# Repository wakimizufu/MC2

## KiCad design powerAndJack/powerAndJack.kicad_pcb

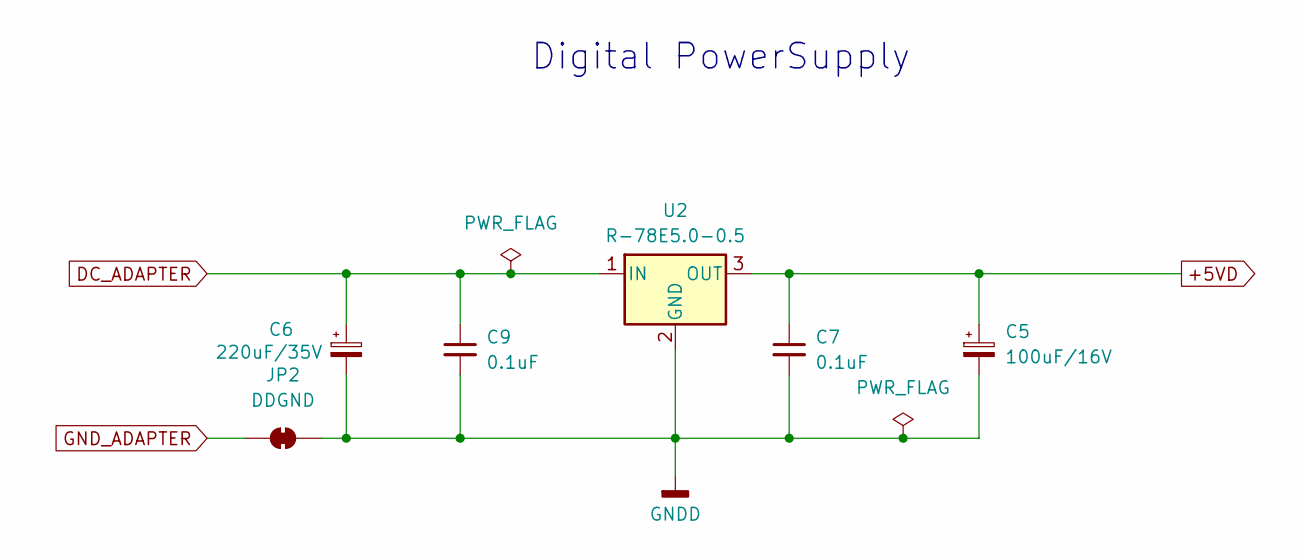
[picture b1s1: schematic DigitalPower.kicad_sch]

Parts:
C5: 100uF/16V; CP_Radial_D5.0mm_P2.00mm
C6: 220uF/35V; CP_Radial_D8.0mm_P3.50mm
C7, C9: 0.1uF; C_0805_2012Metric_Pad1.18x1.45mm_HandSolder
JP2: DDGND; SolderJumper-2_P1.3mm_Bridged2Bar_RoundedPad1.0x1.5mm
U2: R-78E5.0-0.5; Converter_DCDC_RECOM_R-78E-0.5_THT

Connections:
+5VD: C5.1, C7.1, U2.3 (OUT); also elsewhere on the board
DC_ADAPTER: C6.1, C9.1, U2.1 (IN); also elsewhere on the board
GNDD: C5.2, C6.2, C7.2, C9.2, JP2.2 (B), U2.2 (GND); also elsewhere on the board
GND_ADAPTER: JP2.1 (A); also elsewhere on the board

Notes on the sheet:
Digital PowerSupply

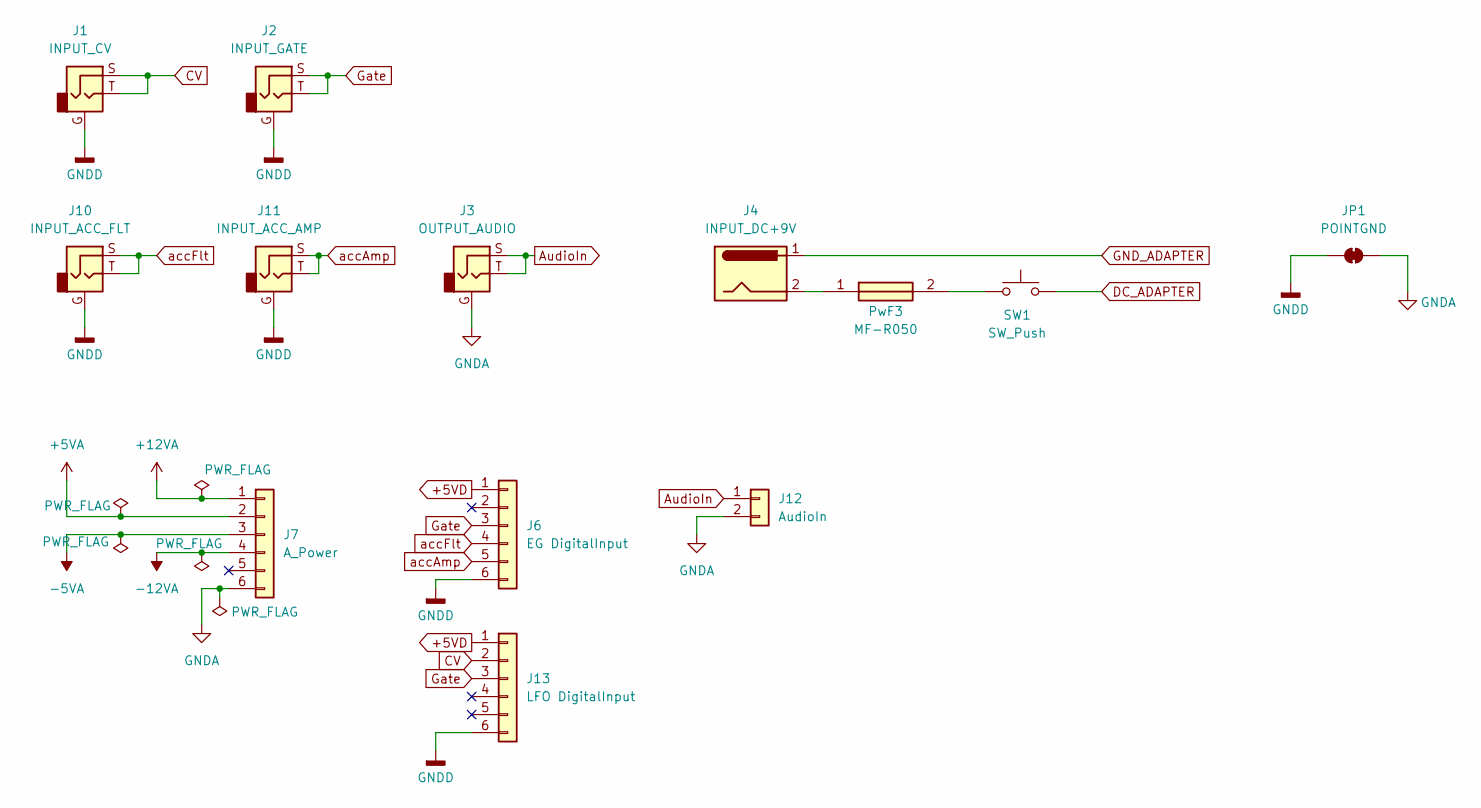
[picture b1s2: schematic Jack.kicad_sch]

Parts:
J1: INPUT_CV; MJ-355W
J2: INPUT_GATE; MJ-355W
J3: OUTPUT_AUDIO; MJ-355W
J4: INPUT_DC+9V; MJ-14
J6: EG DigitalInput; PinHeader_1x06_P2.54mm_Horizontal
J7: A_Power; PinHeader_1x06_P2.54mm_Horizontal
J10: INPUT_ACC_FLT; MJ-355W
J11: INPUT_ACC_AMP; MJ-355W
J12: AudioIn; PinHeader_1x02_P2.54mm_Horizontal
J13: LFO DigitalInput; PinHeader_1x06_P2.54mm_Horizontal
JP1: POINTGND; SolderJumper-2_P1.3mm_Bridged2Bar_RoundedPad1.0x1.5mm
PwF3: MF-R050; MFR050; Manufacturer_Part_Number MF-R050; Mouser Part Number 652-MFR050
SW1: SW_Push; mitumi DS660RC

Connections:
+5VA: J7.2; also elsewhere on the board
+5VD: J6.1, J13.1; also elsewhere on the board
+12VA: J7.1; also elsewhere on the board
-5VA: J7.3; also elsewhere on the board
-12VA: J7.4; also elsewhere on the board
AudioIn: J3.S, J3.T, J12.1
CV: J1.S, J1.T, J13.2
DC_ADAPTER: SW1.2; also elsewhere on the board
GNDA: J3.G, J7.6, J12.2, JP1.2 (B); also elsewhere on the board
GNDD: J1.G, J2.G, J6.6, J10.G, J11.G, J13.6, JP1.1 (A); also elsewhere on the board
GND_ADAPTER: J4.1; also elsewhere on the board
Gate: J2.S, J2.T, J6.3, J13.3
unnamed: J4.2, PwF3.1
unnamed: PwF3.2, SW1.1
accAmp: J6.5, J11.S, J11.T
accFlt: J6.4, J10.S, J10.T

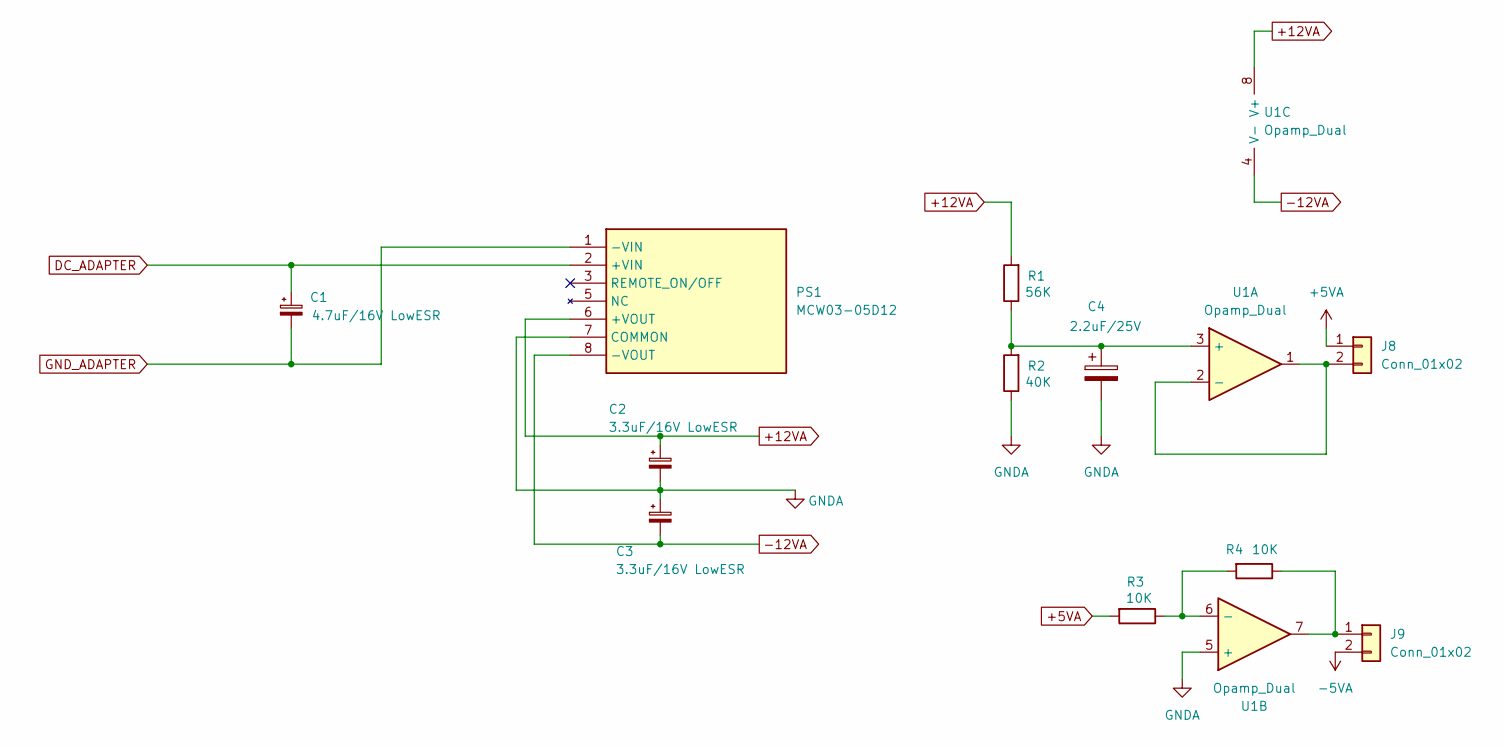
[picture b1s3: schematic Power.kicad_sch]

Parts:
C1: 4.7uF/16V LowESR; CP_Radial_D5.0mm_P2.50mm
C2, C3: 3.3uF/16V LowESR; CP_Radial_D5.0mm_P2.50mm
C4: 2.2uF/25V; CP_Radial_D5.0mm_P2.50mm
J8, J9: Conn_01x02; PinHeader_1x02_P2.54mm_Vertical
PS1: MCW03-05D12; MCW0305D12; Manufacturer_Part_Number MCW03-05D12
R1: 56K; R_Axial_DIN0207_L6.3mm_D2.5mm_P2.54mm_Vertical
R2: 40K; R_Axial_DIN0207_L6.3mm_D2.5mm_P2.54mm_Vertical
R3, R4: 10K; R_Axial_DIN0207_L6.3mm_D2.5mm_P2.54mm_Vertical
U1: Opamp_Dual; SOIC-8_3.9x4.9mm_P1.27mm

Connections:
+5VA: J8.1, R3.2; also elsewhere on the board
+12VA: C2.1, PS1.6 (+VOUT), R1.2, U1.8 (V+); also elsewhere on the board
-5VA: J9.2; also elsewhere on the board
-12VA: C3.2, PS1.8 (-VOUT), U1.4 (V-); also elsewhere on the board
DC_ADAPTER: C1.1, PS1.2 (+VIN); also elsewhere on the board
GNDA: C2.2, C3.1, C4.2, PS1.7 (COMMON), R2.1, U1.5 (+); also elsewhere on the board
GND_ADAPTER: C1.2, PS1.1 (-VIN); also elsewhere on the board
unnamed: J8.2, U1.1, U1.2 (-)
unnamed: J9.1, R4.1, U1.7
unnamed: C4.1, R1.1, R2.2, U1.3 (+)
unnamed: R3.1, R4.2, U1.6 (-)

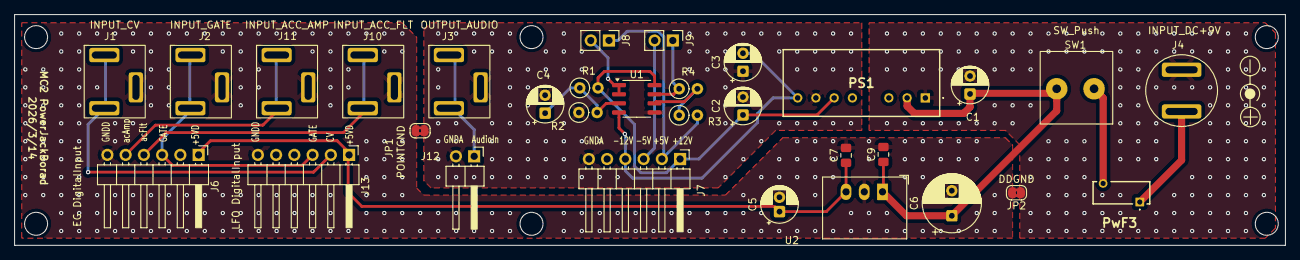
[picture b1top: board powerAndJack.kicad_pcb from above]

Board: 2 copper layers, 177.0 x 32.1 mm, 31 parts (0 on the bottom side), 20 nets.

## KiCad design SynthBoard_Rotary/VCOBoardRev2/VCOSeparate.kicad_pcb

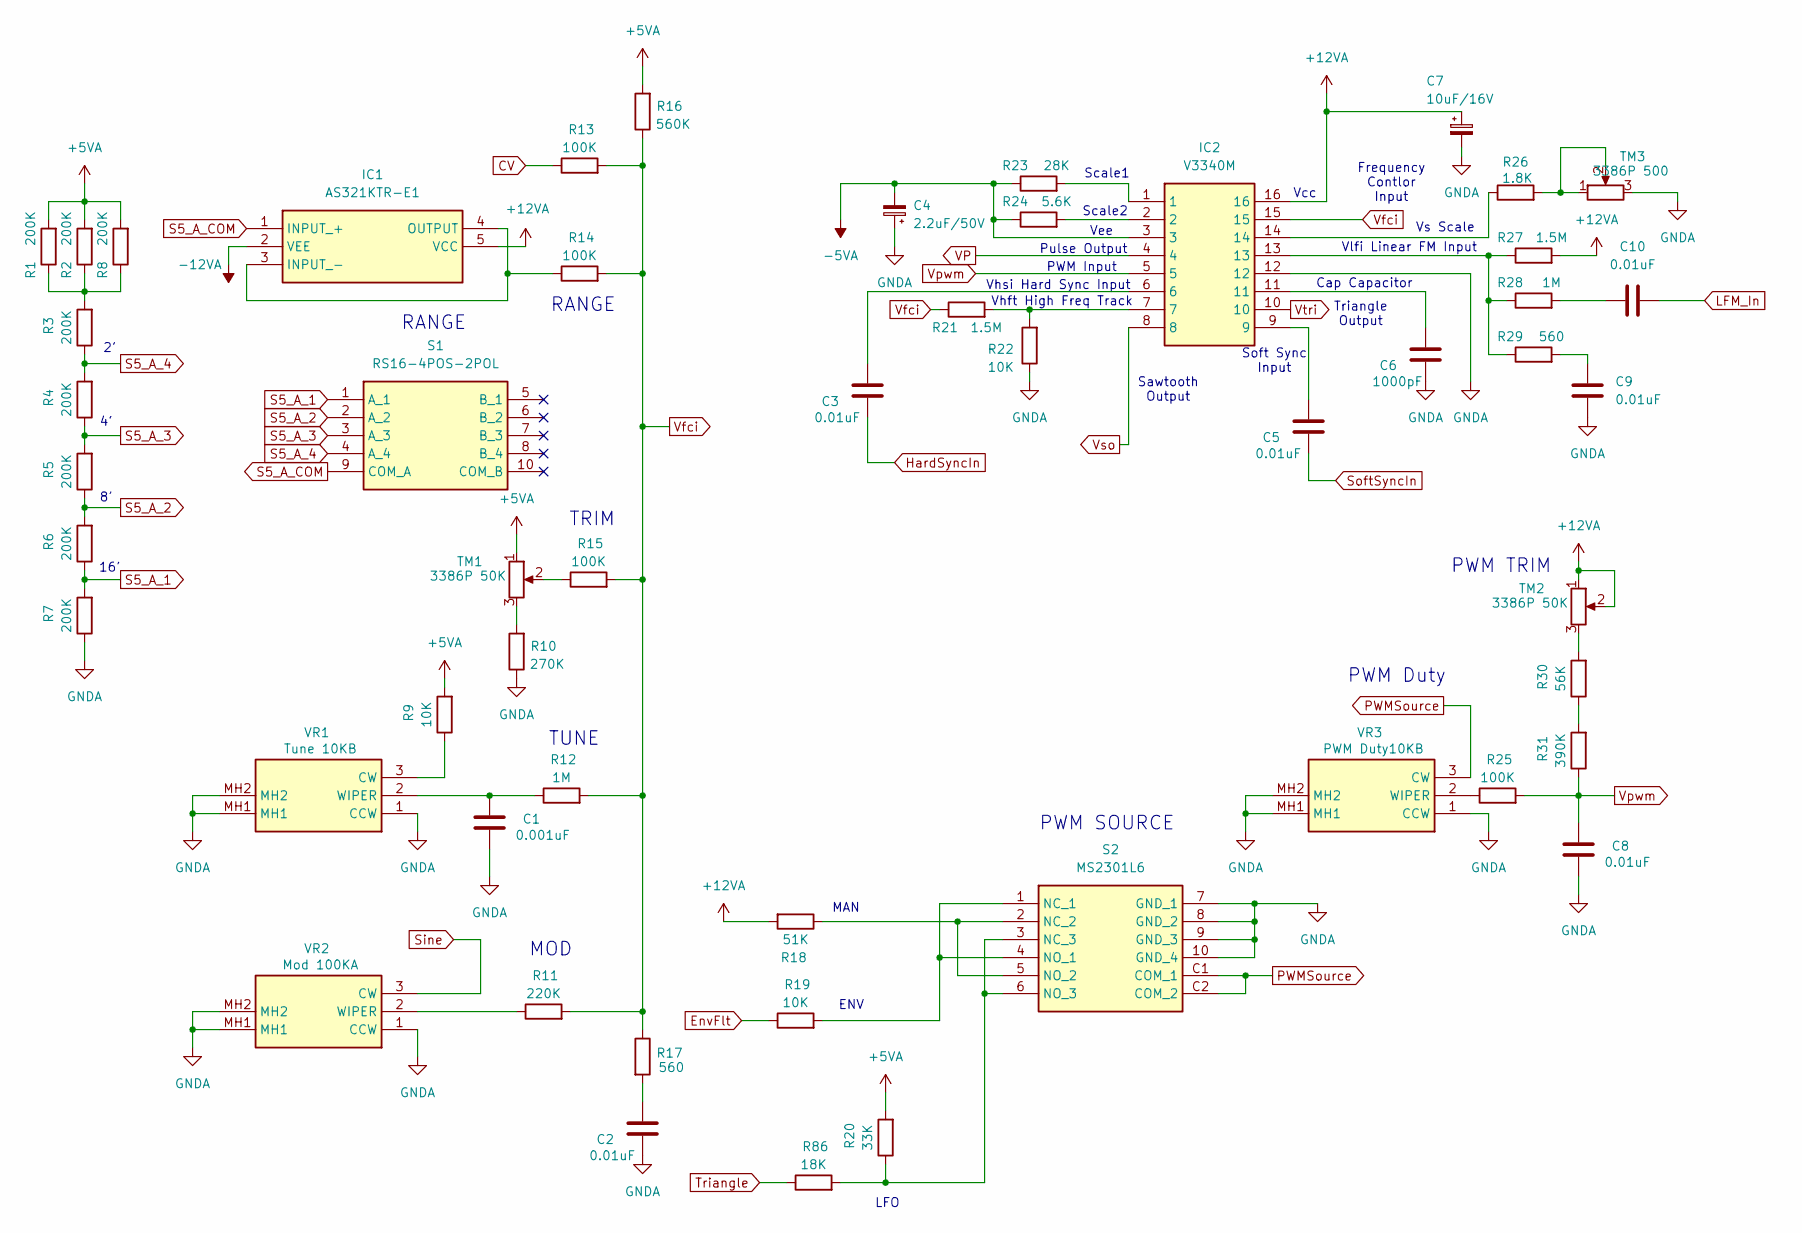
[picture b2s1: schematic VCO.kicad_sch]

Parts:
C1: 0.001uF; C_Disc_D5.0mm_W2.5mm_P2.50mm
C2, C3, C5, C8, C9, C10: 0.01uF; C_Disc_D5.0mm_W2.5mm_P2.50mm
C4: 2.2uF/50V; CP_Radial_D5.0mm_P2.50mm
C6: 1000pF; C_Disc_D5.0mm_W2.5mm_P2.50mm
C7: 10uF/16V; CP_Radial_D5.0mm_P2.50mm
IC1: AS321KTR-E1; SOT95P282X145-5N; Manufacturer_Part_Number AS321KTR-E1; Mouser Part Number 621-AS321KTR-E1
IC2: V3340M; SOP-16_3.9x9.9mm_P1.27mm; Manufacturer_Part_Number V3340M
R1, R2, R3, R4, R5, R6, R7, R8: 200K; R_Axial_DIN0207_L6.3mm_D2.5mm_P2.54mm_Vertical
R9, R19, R22: 10K; R_Axial_DIN0207_L6.3mm_D2.5mm_P2.54mm_Vertical
R10: 270K; R_Axial_DIN0207_L6.3mm_D2.5mm_P2.54mm_Vertical
R11: 220K; R_Axial_DIN0207_L6.3mm_D2.5mm_P2.54mm_Vertical
R12, R28: 1M; R_Axial_DIN0207_L6.3mm_D2.5mm_P2.54mm_Vertical
R13, R14, R15, R25: 100K; R_Axial_DIN0207_L6.3mm_D2.5mm_P2.54mm_Vertical
R16: 560K; R_Axial_DIN0207_L6.3mm_D2.5mm_P2.54mm_Vertical
R17, R29: 560; R_Axial_DIN0207_L6.3mm_D2.5mm_P2.54mm_Vertical
R18: 51K; R_Axial_DIN0207_L6.3mm_D2.5mm_P2.54mm_Vertical
R20: 33K; R_Axial_DIN0207_L6.3mm_D2.5mm_P2.54mm_Vertical
R21, R27: 1.5M; R_Axial_DIN0207_L6.3mm_D2.5mm_P2.54mm_Vertical
R23: 28K; R_Axial_DIN0207_L6.3mm_D2.5mm_P2.54mm_Vertical
R24: 5.6K; R_Axial_DIN0207_L6.3mm_D2.5mm_P2.54mm_Vertical
R26: 1.8K; R_Axial_DIN0207_L6.3mm_D2.5mm_P2.54mm_Vertical
R30: 56K; R_Axial_DIN0207_L6.3mm_D2.5mm_P2.54mm_Vertical
R31: 390K; R_Axial_DIN0207_L6.3mm_D2.5mm_P2.54mm_Vertical
R86: 18K; R_Axial_DIN0207_L6.3mm_D2.5mm_P2.54mm_Vertical
S1: RS16-4POS-2POL; RS164POS2POL; Manufacturer_Part_Number RS16-4POS-2POL
S2: MS2301L6; Manufacturer_Part_Number MS2301L6
TM1, TM2: 3386P 50K; Potentiometer_Bourns_3386P_Vertical
TM3: 3386P 500; Potentiometer_Bourns_3386P_Vertical
VR1: Tune 10KB; RK09D117000B; Manufacturer_Part_Number RK09D117000B; Mouser Part Number 688-RK09D117000B
VR2: Mod 100KA; RK09D117000B; Manufacturer_Part_Number RK09D117000B; Mouser Part Number 688-RK09D117000B
VR3: PWM Duty10KB; RK09D117000B; Manufacturer_Part_Number RK09D117000B; Mouser Part Number 688-RK09D117000B

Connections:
+5VA: R1.2, R2.2, R8.2, R9.2, R16.2, R20.2, TM1.1; also elsewhere on the board
+12VA: C7.1, IC1.5 (VCC), IC2.16, R18.2, R27.2, TM2.1, TM2.2; also elsewhere on the board
-5VA: C4.2, IC2.3, R23.1, R24.1; also elsewhere on the board
-12VA: IC1.2 (VEE); also elsewhere on the board
CV: R13.1; also elsewhere on the board
EnvFlt: R19.1; also elsewhere on the board
GNDA: C1.1, C2.1, C4.1, C6.1, C7.2, C8.1, C9.1, IC2.12, R7.1, R10.1, R22.1, S2.7 (GND_1), S2.8 (GND_2), S2.9 (GND_3), S2.10 (GND_4), TM3.3, VR1.1 (CCW), VR1.MH1, VR1.MH2, VR2.1 (CCW), VR2.MH1, VR2.MH2, VR3.1 (CCW), VR3.MH1, VR3.MH2; also elsewhere on the board
HardSyncIn: C3.1; also elsewhere on the board
LFM_In: C10.1; also elsewhere on the board
unnamed: C2.2, R17.2
unnamed: C3.2, IC2.6
unnamed: C5.2, IC2.9
unnamed: C6.2, IC2.11
unnamed: C9.2, R29.2
unnamed: C10.2, R28.2
unnamed: IC1.3 (INPUT_-), IC1.4 (OUTPUT), R14.1
unnamed: IC2.1, R23.2
unnamed: IC2.2, R24.2
unnamed: IC2.7, R21.2, R22.2
unnamed: IC2.13, R27.1, R28.1, R29.1
unnamed: IC2.14, R26.1
unnamed: R1.1, R2.1, R3.2, R8.1
unnamed: R10.2, TM1.3
unnamed: R15.1, TM1.2
unnamed: R26.2, TM3.1, TM3.2
unnamed: R30.1, R31.2
unnamed: R30.2, TM2.3
unnamed: R19.2, S2.1 (NC_1), S2.4 (NO_1)
unnamed: R18.1, S2.2 (NC_2), S2.5 (NO_2)
unnamed: R20.1, R86.2, S2.3 (NC_3), S2.6 (NO_3)
unnamed: R9.1, VR1.3 (CW)
unnamed: C1.2, R12.1, VR1.2 (WIPER)
unnamed: R11.1, VR2.2 (WIPER)
unnamed: R25.1, VR3.2 (WIPER)
PWMSource: S2.C1 (COM_1), S2.C2 (COM_2), VR3.3 (CW)
S5_A_1: R6.1, R7.2, S1.1 (A_1)
S5_A_2: R5.1, R6.2, S1.2 (A_2)
S5_A_3: R4.1, R5.2, S1.3 (A_3)
S5_A_4: R3.1, R4.2, S1.4 (A_4)
S5_A_COM: IC1.1 (INPUT_+), S1.9 (COM_A)
Sine: VR2.3 (CW); also elsewhere on the board
SoftSyncIn: C5.1; also elsewhere on the board
Triangle: R86.1; also elsewhere on the board
VP: IC2.4; also elsewhere on the board
Vfci: IC2.15, R11.2, R12.2, R13.2, R14.2, R15.2, R16.1, R17.1, R21.1
Vpwm: C8.2, IC2.5, R25.2, R31.1
Vso: IC2.8; also elsewhere on the board
Vtri: IC2.10; also elsewhere on the board

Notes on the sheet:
Vhft High Freq Track
LFO
TRIM
MOD
Vee
MAN
Sawtooth Output
PWM Input
RANGE
Vcc
PWM SOURCE
Vhsi Hard Sync Input
PWM TRIM
Vlfi Linear FM Input
16'
Pulse Output
Vs Scale
Scale1
Scale2
Triangle Output
Cap Capacitor
PWM Duty
Frequency Contlor Input
Soft Sync Input
TUNE
ENV

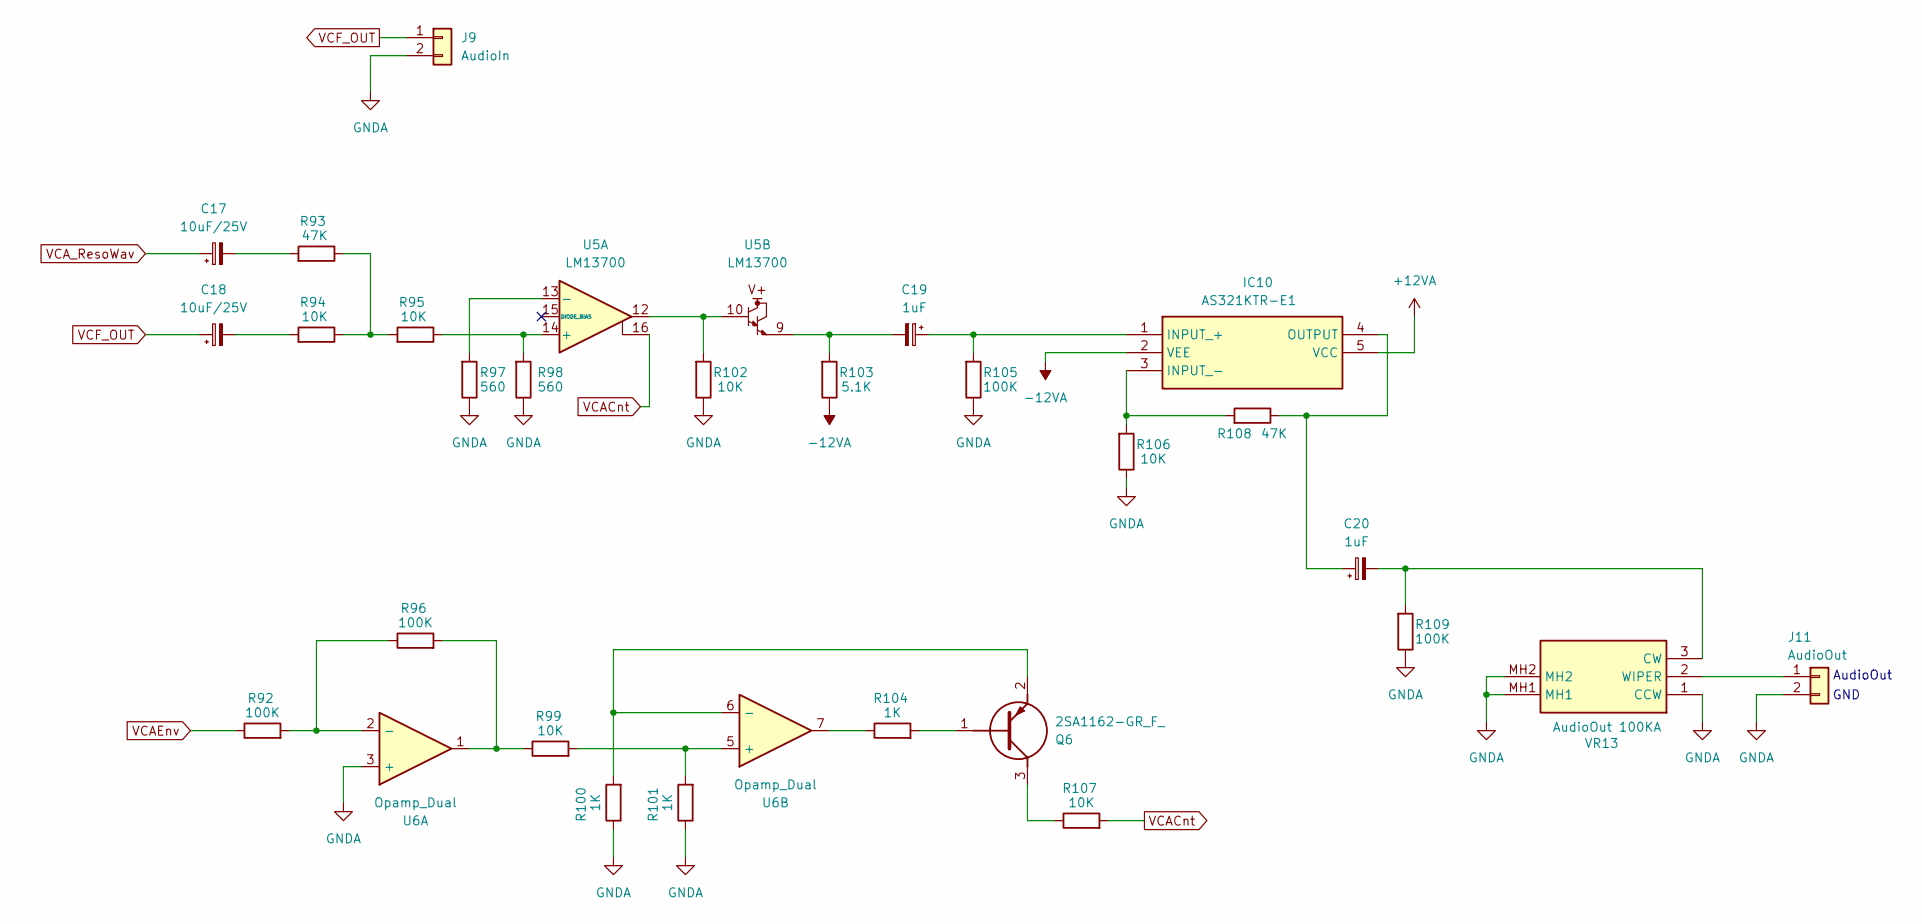
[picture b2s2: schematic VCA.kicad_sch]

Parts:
C17, C18: 10uF/25V; CP_Radial_D5.0mm_P2.50mm
C19, C20: 1uF; CP_Radial_D5.0mm_P2.50mm
IC10: AS321KTR-E1; SOT95P282X145-5N; Manufacturer_Part_Number AS321KTR-E1; Mouser Part Number 621-AS321KTR-E1
J9: AudioIn; PinSocket_1x02_P2.54mm_Vertical
J11: AudioOut; PinHeader_1x02_P2.54mm_Vertical
Q6: 2SA1162-GR_F_; 1SS294LFT; Manufacturer_Part_Number 2SA1162-GR(F)
R92, R96, R105, R109: 100K; R_Axial_DIN0207_L6.3mm_D2.5mm_P2.54mm_Vertical
R93, R108: 47K; R_Axial_DIN0207_L6.3mm_D2.5mm_P2.54mm_Vertical
R94, R95, R99, R102, R106, R107: 10K; R_Axial_DIN0207_L6.3mm_D2.5mm_P2.54mm_Vertical
R97, R98: 560; R_Axial_DIN0207_L6.3mm_D2.5mm_P2.54mm_Vertical
R100, R101, R104: 1K; R_Axial_DIN0207_L6.3mm_D2.5mm_P2.54mm_Vertical
R103: 5.1K; R_Axial_DIN0207_L6.3mm_D2.5mm_P2.54mm_Vertical
U5: LM13700; SOIC-16_3.9x9.9mm_P1.27mm
U6: Opamp_Dual; SOIC-8_3.9x4.9mm_P1.27mm
VR13: AudioOut 100KA; RK09D117000B; Manufacturer_Part_Number RK09D117000B; Mouser Part Number 688-RK09D117000B

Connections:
+12VA: IC10.5 (VCC); also elsewhere on the board
-12VA: IC10.2 (VEE), R103.1; also elsewhere on the board
GNDA: J9.2, J11.2, R97.1, R98.1, R100.1, R101.1, R102.1, R105.1, R106.1, R109.1, U6.3 (+), VR13.1 (CCW), VR13.MH1, VR13.MH2; also elsewhere on the board
unnamed: C17.2, R93.2
unnamed: C18.2, R94.2
unnamed: C19.2, R103.2, U5.9
unnamed: C19.1, IC10.1 (INPUT_+), R105.2
unnamed: IC10.3 (INPUT_-), R106.2, R108.2
unnamed: C20.1, IC10.4 (OUTPUT), R108.1
unnamed: J11.1, VR13.2 (WIPER)
unnamed: Q6.1 (B), R104.2
unnamed: Q6.3 (C), R107.1
unnamed: Q6.2 (E), R100.2, U6.6 (-)
unnamed: R93.1, R94.1, R95.2
unnamed: R96.2, R99.1, U6.1
unnamed: R102.2, U5.10, U5.12
unnamed: R104.1, U6.7
unnamed: R95.1, R98.2, U5.14 (+)
unnamed: R97.2, U5.13 (-)
unnamed: R92.2, R96.1, U6.2 (-)
unnamed: R99.2, R101.2, U6.5 (+)
unnamed: C20.2, R109.2, VR13.3 (CW)
VCACnt: R107.2, U5.16
VCAEnv: R92.1; also elsewhere on the board
VCA_ResoWav: C17.1; also elsewhere on the board
VCF_OUT: C18.1, J9.1; also elsewhere on the board

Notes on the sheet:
AudioOut
GND

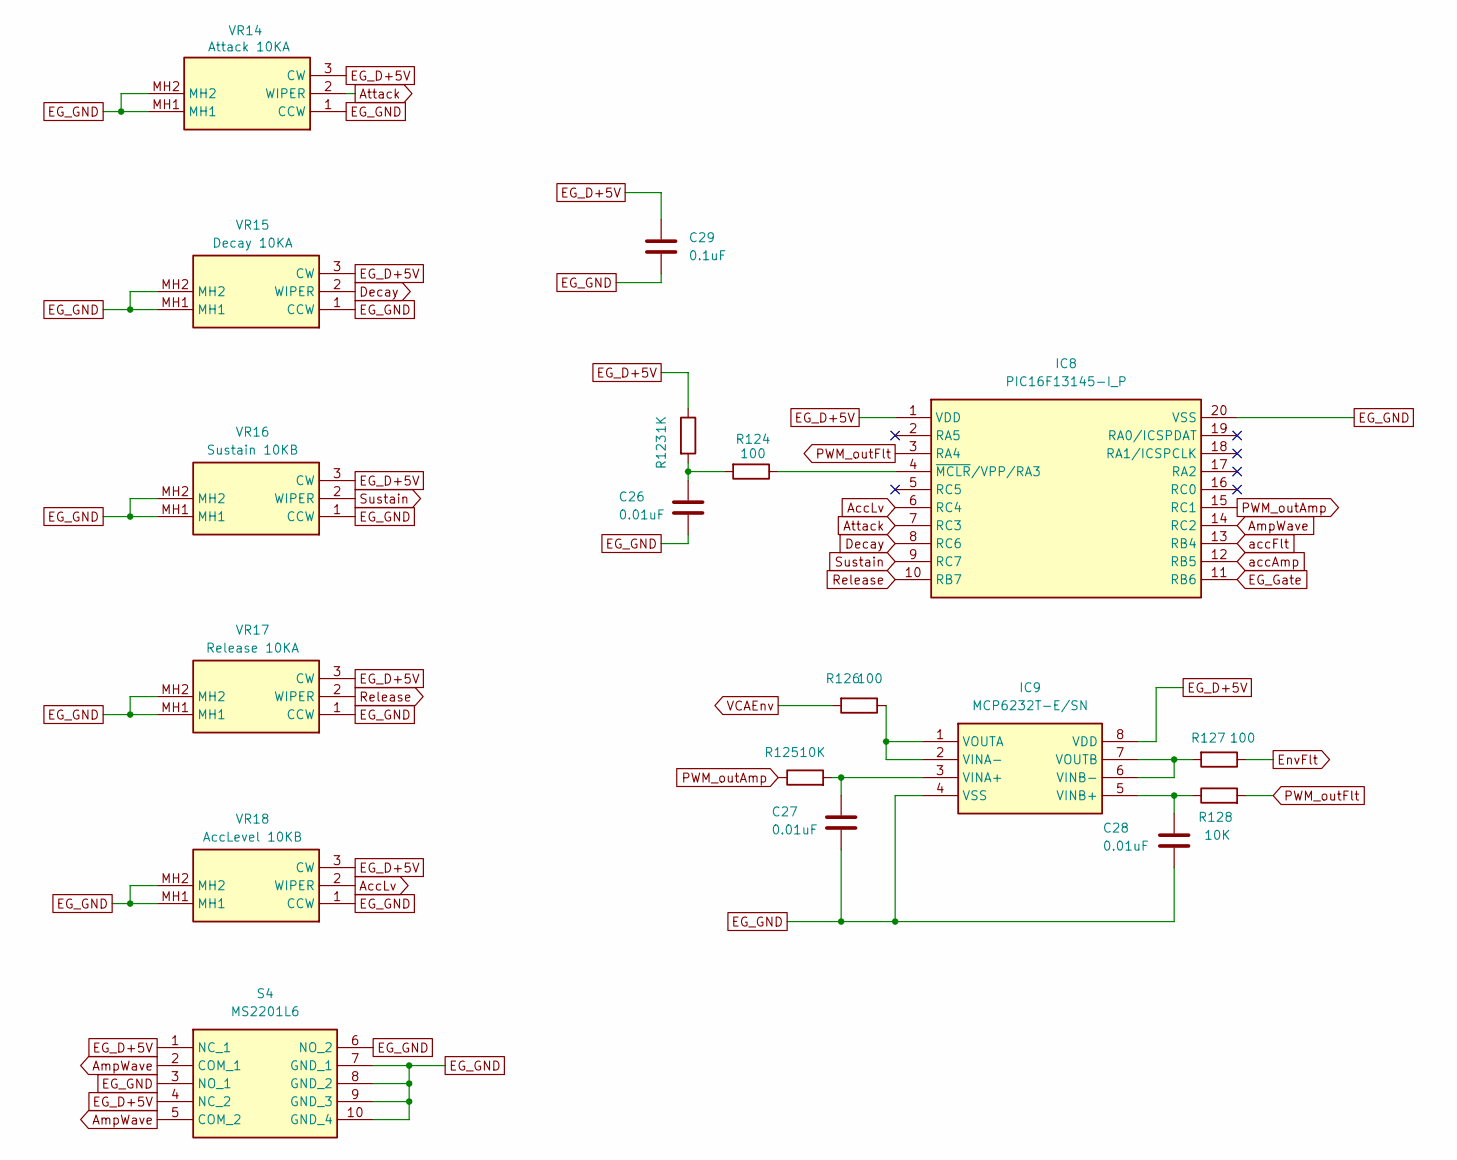
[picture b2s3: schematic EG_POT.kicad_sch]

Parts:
C26, C27, C28: 0.01uF; C_Disc_D4.3mm_W1.9mm_P5.00mm
C29: 0.1uF; C_0805_2012Metric_Pad1.18x1.45mm_HandSolder
IC8: PIC16F13145-I_P; DIP794W56P254L2591H533Q20N; Manufacturer_Part_Number PIC16F13145-I/P; Mouser Part Number 579-PIC16F13145-I/P
IC9: MCP6232T-E/SN; SOIC-8_3.9x4.9mm_P1.27mm; Manufacturer_Part_Number MCP6232-E/P; Mouser Part Number 579-MCP6232-E/P
R123: 1K; R_Axial_DIN0204_L3.6mm_D1.6mm_P2.54mm_Vertical
R124, R126, R127: 100; R_Axial_DIN0204_L3.6mm_D1.6mm_P2.54mm_Vertical
R125, R128: 10K; R_Axial_DIN0204_L3.6mm_D1.6mm_P2.54mm_Vertical
S4: MS2201L6; Manufacturer_Part_Number MS2201L6
VR14: Attack 10KA; RK09D117000B; Manufacturer_Part_Number RK09D117000B; Mouser Part Number 688-RK09D117000B
VR15: Decay 10KA; RK09D117000B; Manufacturer_Part_Number RK09D117000B; Mouser Part Number 688-RK09D117000B
VR16: Sustain 10KB; RK09D117000B; Manufacturer_Part_Number RK09D117000B; Mouser Part Number 688-RK09D117000B
VR17: Release 10KA; RK09D117000B; Manufacturer_Part_Number RK09D117000B; Mouser Part Number 688-RK09D117000B
VR18: AccLevel 10KB; RK09D117000B; Manufacturer_Part_Number RK09D117000B; Mouser Part Number 688-RK09D117000B

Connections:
AccLv: IC8.6 (RC4), VR18.2 (WIPER)
AmpWave: IC8.14 (RC2), S4.2 (COM_1), S4.5 (COM_2)
Attack: IC8.7 (RC3), VR14.2 (WIPER)
Decay: IC8.8 (RC6), VR15.2 (WIPER)
EG_D+5V: C29.1, IC8.1 (VDD), IC9.8 (VDD), R123.1, S4.1 (NC_1), S4.4 (NC_2), VR14.3 (CW), VR15.3 (CW), VR16.3 (CW), VR17.3 (CW), VR18.3 (CW); also elsewhere on the board
EG_GND: C26.2, C27.2, C28.2, C29.2, IC8.20 (VSS), IC9.4 (VSS), S4.3 (NO_1), S4.6 (NO_2), S4.7 (GND_1), S4.8 (GND_2), S4.9 (GND_3), S4.10 (GND_4), VR14.1 (CCW), VR14.MH1, VR14.MH2, VR15.1 (CCW), VR15.MH1, VR15.MH2, VR16.1 (CCW), VR16.MH1, VR16.MH2, VR17.1 (CCW), VR17.MH1, VR17.MH2, VR18.1 (CCW), VR18.MH1, VR18.MH2; also elsewhere on the board
EG_Gate: IC8.11 (RB6); also elsewhere on the board
EnvFlt: R127.1; also elsewhere on the board
unnamed: C26.1, R123.2, R124.2
unnamed: IC8.4 (~MCLR/VPP/RA3), R124.1
unnamed: C27.1, IC9.3 (VINA+), R125.2
unnamed: IC9.1 (VOUTA), IC9.2 (VINA-), R126.1
unnamed: C28.1, IC9.5 (VINB+), R128.1
unnamed: IC9.6 (VINB-), IC9.7 (VOUTB), R127.2
PWM_outAmp: IC8.15 (RC1), R125.1
PWM_outFlt: IC8.3 (RA4), R128.2
Release: IC8.10 (RB7), VR17.2 (WIPER)
Sustain: IC8.9 (RC7), VR16.2 (WIPER)
VCAEnv: R126.2; also elsewhere on the board
accAmp: IC8.12 (RB5); also elsewhere on the board
accFlt: IC8.13 (RB4); also elsewhere on the board

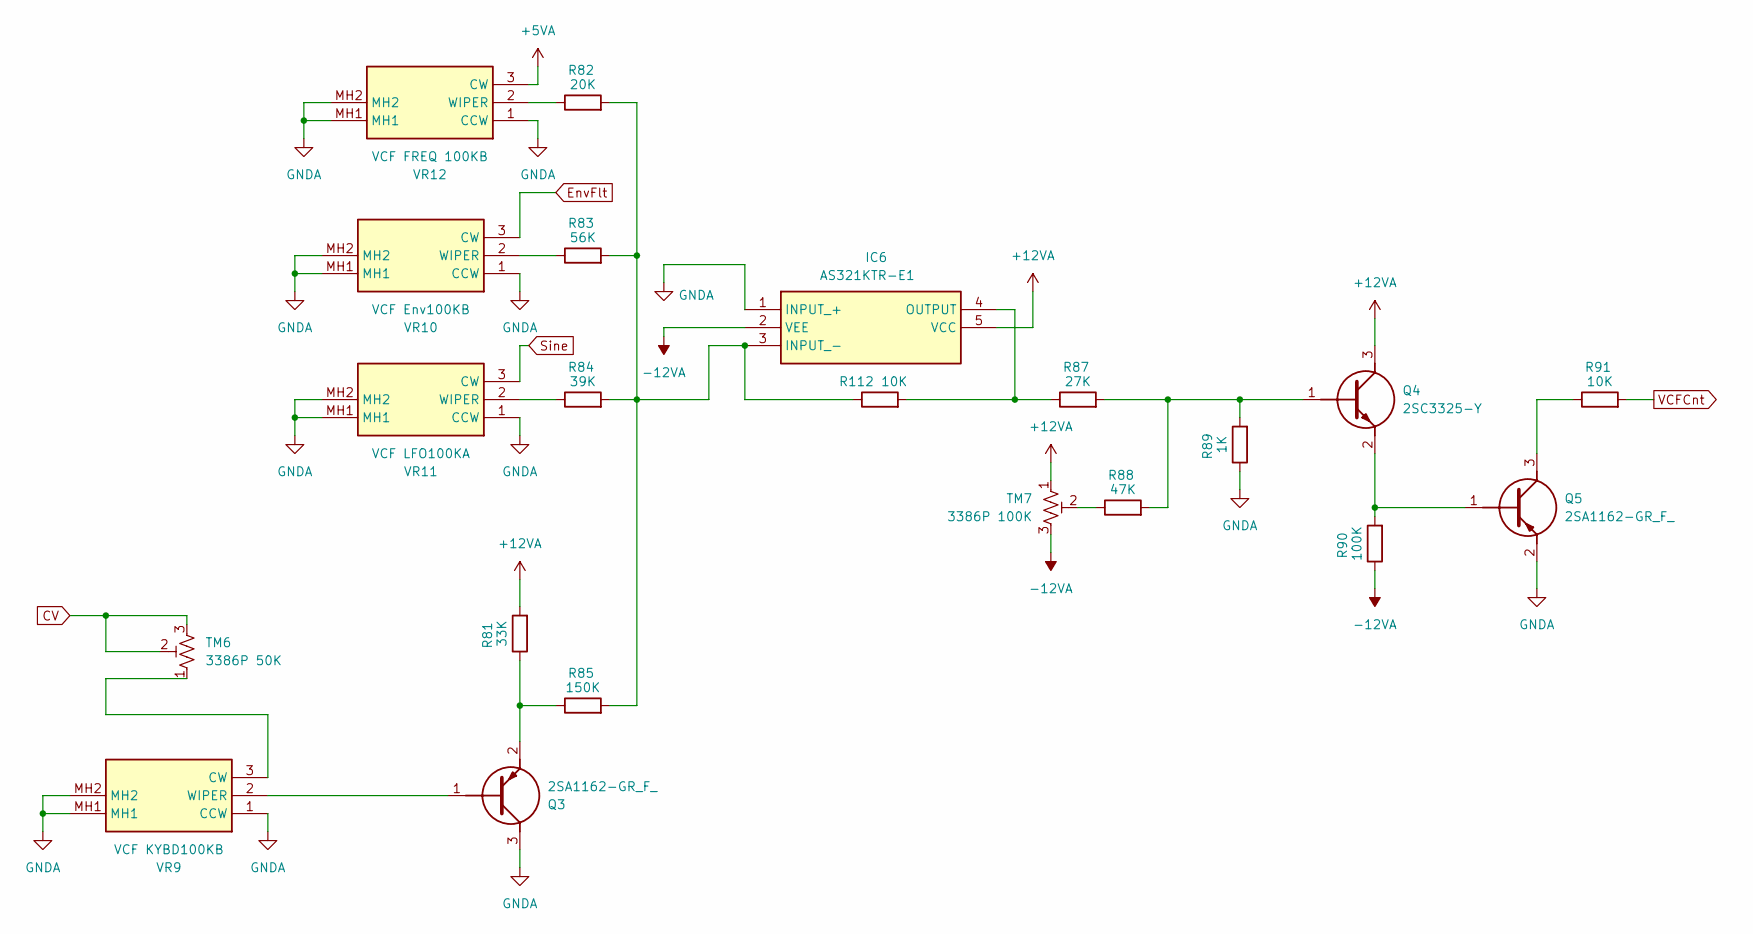
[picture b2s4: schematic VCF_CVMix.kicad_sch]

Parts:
IC6: AS321KTR-E1; SOT95P282X145-5N; Manufacturer_Part_Number AS321KTR-E1; Mouser Part Number 621-AS321KTR-E1
Q3, Q5: 2SA1162-GR_F_; 1SS294LFT; Manufacturer_Part_Number 2SA1162-GR(F)
Q4: 2SC3325-Y; 2SC3325YLF; Manufacturer_Part_Number 2SC3325-Y
R81: 33K; R_Axial_DIN0207_L6.3mm_D2.5mm_P2.54mm_Vertical
R82: 20K; R_Axial_DIN0207_L6.3mm_D2.5mm_P2.54mm_Vertical
R83: 56K; R_Axial_DIN0207_L6.3mm_D2.5mm_P2.54mm_Vertical
R84: 39K; R_Axial_DIN0207_L6.3mm_D2.5mm_P2.54mm_Vertical
R85: 150K; R_Axial_DIN0207_L6.3mm_D2.5mm_P2.54mm_Vertical
R87: 27K; R_Axial_DIN0207_L6.3mm_D2.5mm_P2.54mm_Vertical
R88: 47K; R_Axial_DIN0207_L6.3mm_D2.5mm_P2.54mm_Vertical
R89: 1K; R_Axial_DIN0207_L6.3mm_D2.5mm_P2.54mm_Vertical
R90: 100K; R_Axial_DIN0207_L6.3mm_D2.5mm_P2.54mm_Vertical
R91, R112: 10K; R_Axial_DIN0207_L6.3mm_D2.5mm_P2.54mm_Vertical
TM6: 3386P 50K; Potentiometer_Bourns_3386P_Vertical
TM7: 3386P 100K; Potentiometer_Bourns_3386P_Vertical
VR9: VCF KYBD100KB; RK09D117000B; Manufacturer_Part_Number RK09D117000B; Mouser Part Number 688-RK09D117000B
VR10: VCF Env100KB; RK09D117000B; Manufacturer_Part_Number RK09D117000B; Mouser Part Number 688-RK09D117000B
VR11: VCF LFO100KA; RK09D117000B; Manufacturer_Part_Number RK09D117000B; Mouser Part Number 688-RK09D117000B
VR12: VCF FREQ 100KB; RK09D117000B; Manufacturer_Part_Number RK09D117000B; Mouser Part Number 688-RK09D117000B

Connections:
+5VA: VR12.3 (CW); also elsewhere on the board
+12VA: IC6.5 (VCC), Q4.3 (C), R81.2, TM7.1; also elsewhere on the board
-12VA: IC6.2 (VEE), R90.1, TM7.3; also elsewhere on the board
CV: TM6.2, TM6.3; also elsewhere on the board
EnvFlt: VR10.3 (CW); also elsewhere on the board
GNDA: IC6.1 (INPUT_+), Q3.3 (C), Q5.2 (E), R89.1, VR9.1 (CCW), VR9.MH1, VR9.MH2, VR10.1 (CCW), VR10.MH1, VR10.MH2, VR11.1 (CCW), VR11.MH1, VR11.MH2, VR12.1 (CCW), VR12.MH1, VR12.MH2; also elsewhere on the board
unnamed: IC6.3 (INPUT_-), R82.2, R83.2, R84.2, R85.2, R112.1
unnamed: IC6.4 (OUTPUT), R87.1, R112.2
unnamed: Q3.1 (B), VR9.2 (WIPER)
unnamed: Q3.2 (E), R81.1, R85.1
unnamed: Q4.1 (B), R87.2, R88.2, R89.2
unnamed: Q4.2 (E), Q5.1 (B), R90.2
unnamed: Q5.3 (C), R91.1
unnamed: R88.1, TM7.2
unnamed: TM6.1, VR9.3 (CW)
unnamed: R83.1, VR10.2 (WIPER)
unnamed: R84.1, VR11.2 (WIPER)
unnamed: R82.1, VR12.2 (WIPER)
Sine: VR11.3 (CW); also elsewhere on the board
VCFCnt: R91.2; also elsewhere on the board

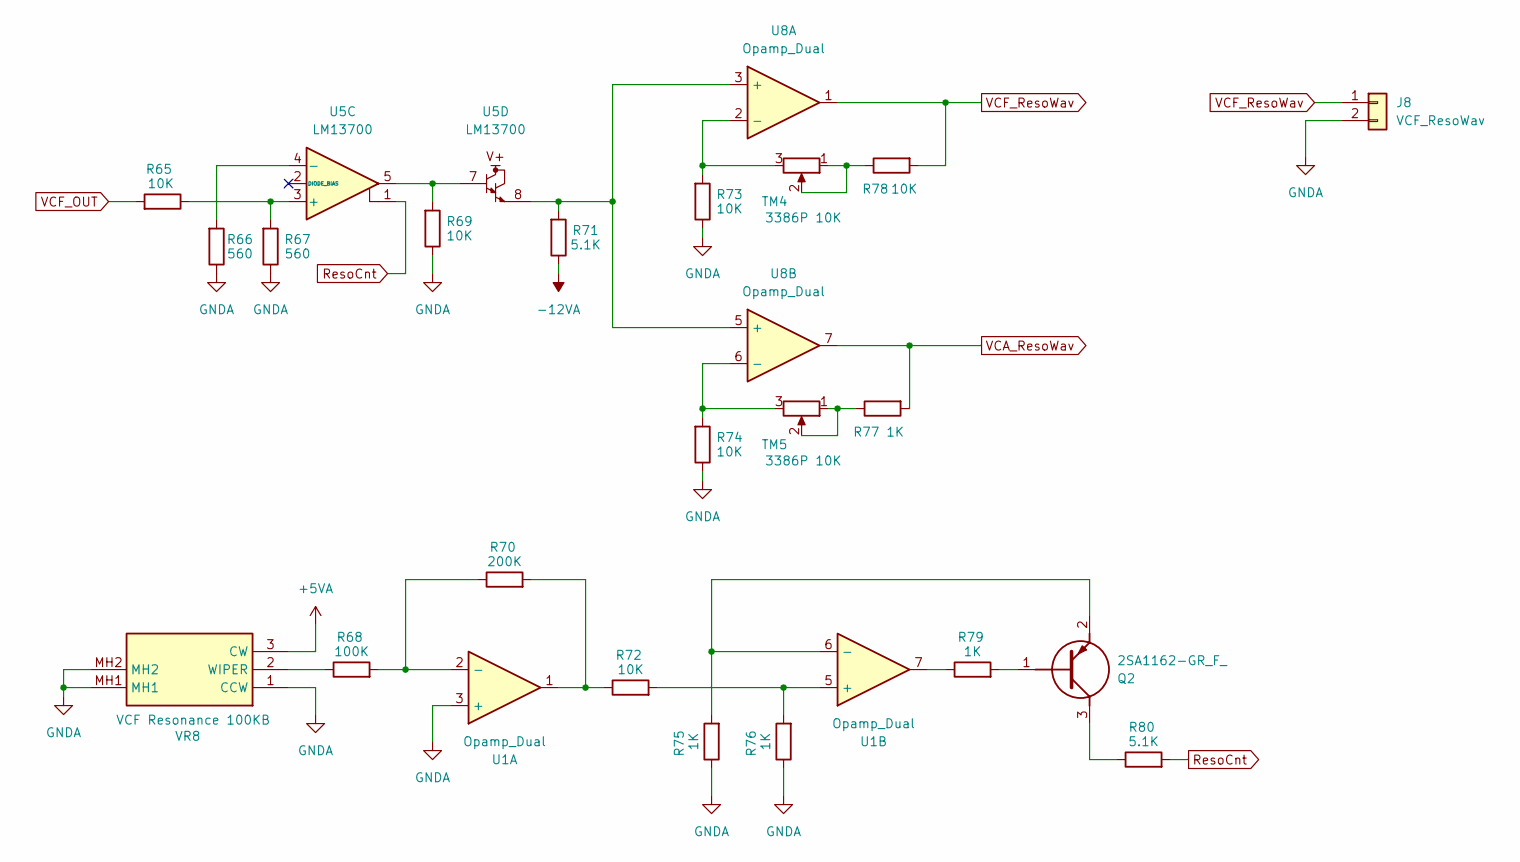
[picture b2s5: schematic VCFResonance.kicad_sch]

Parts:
J8: VCF_ResoWav; PinSocket_1x02_P2.54mm_Vertical
Q2: 2SA1162-GR_F_; 1SS294LFT; Manufacturer_Part_Number 2SA1162-GR(F)
R65, R69, R72, R73, R74, R78: 10K; R_Axial_DIN0207_L6.3mm_D2.5mm_P2.54mm_Vertical
R66, R67: 560; R_Axial_DIN0207_L6.3mm_D2.5mm_P2.54mm_Vertical
R68: 100K; R_Axial_DIN0207_L6.3mm_D2.5mm_P2.54mm_Vertical
R70: 200K; R_Axial_DIN0207_L6.3mm_D2.5mm_P2.54mm_Vertical
R71, R80: 5.1K; R_Axial_DIN0207_L6.3mm_D2.5mm_P2.54mm_Vertical
R75, R76, R77, R79: 1K; R_Axial_DIN0207_L6.3mm_D2.5mm_P2.54mm_Vertical
TM4, TM5: 3386P 10K; Potentiometer_Bourns_3386P_Vertical
U1, U8: Opamp_Dual; SOIC-8_3.9x4.9mm_P1.27mm
U5: LM13700; SOIC-16_3.9x9.9mm_P1.27mm
VR8: VCF Resonance 100KB; RK09D117000B; Manufacturer_Part_Number RK09D117000B; Mouser Part Number 688-RK09D117000B

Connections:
+5VA: VR8.3 (CW); also elsewhere on the board
-12VA: R71.1; also elsewhere on the board
GNDA: J8.2, R66.1, R67.1, R69.1, R73.1, R74.1, R75.1, R76.1, U1.3 (+), VR8.1 (CCW), VR8.MH1, VR8.MH2; also elsewhere on the board
unnamed: Q2.1 (B), R79.2
unnamed: Q2.3 (C), R80.1
unnamed: Q2.2 (E), R75.2, U1.6 (-)
unnamed: R69.2, U5.5, U5.7
unnamed: R70.2, R72.1, U1.1
unnamed: R77.1, TM5.1, TM5.2
unnamed: R78.1, TM4.1, TM4.2
unnamed: R79.1, U1.7
unnamed: R68.2, R70.1, U1.2 (-)
unnamed: R72.2, R76.2, U1.5 (+)
unnamed: R65.1, R67.2, U5.3 (+)
unnamed: R66.2, U5.4 (-)
unnamed: R71.2, U5.8, U8.3 (+), U8.5 (+)
unnamed: R73.2, TM4.3, U8.2 (-)
unnamed: R74.2, TM5.3, U8.6 (-)
unnamed: R68.1, VR8.2 (WIPER)
ResoCnt: R80.2, U5.1
VCA_ResoWav: R77.2, U8.7; also elsewhere on the board
VCF_OUT: R65.2; also elsewhere on the board
VCF_ResoWav: J8.1, R78.2, U8.1; also elsewhere on the board
